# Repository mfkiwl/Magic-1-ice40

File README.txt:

These boards are designed to replicate Bill Buzbee's Magic-1 computer at 

http://www.homebrewcpu.com

They are licenced as Open Source Hardware

https://en.wikipedia.org/wiki/Open-source_hardware

Notes:

Cards are 160x233 euro card with 2 DIN 41612 C96 connectors

They are designed to be used in a Schroff EuropacPRO enclosure

The holes on the outside edge of the card (opposite to the connectors)
are designed to accept the Schroff card extractors ref 24560-378
You will also need to add ref 24560-377 for each card slot for this to work

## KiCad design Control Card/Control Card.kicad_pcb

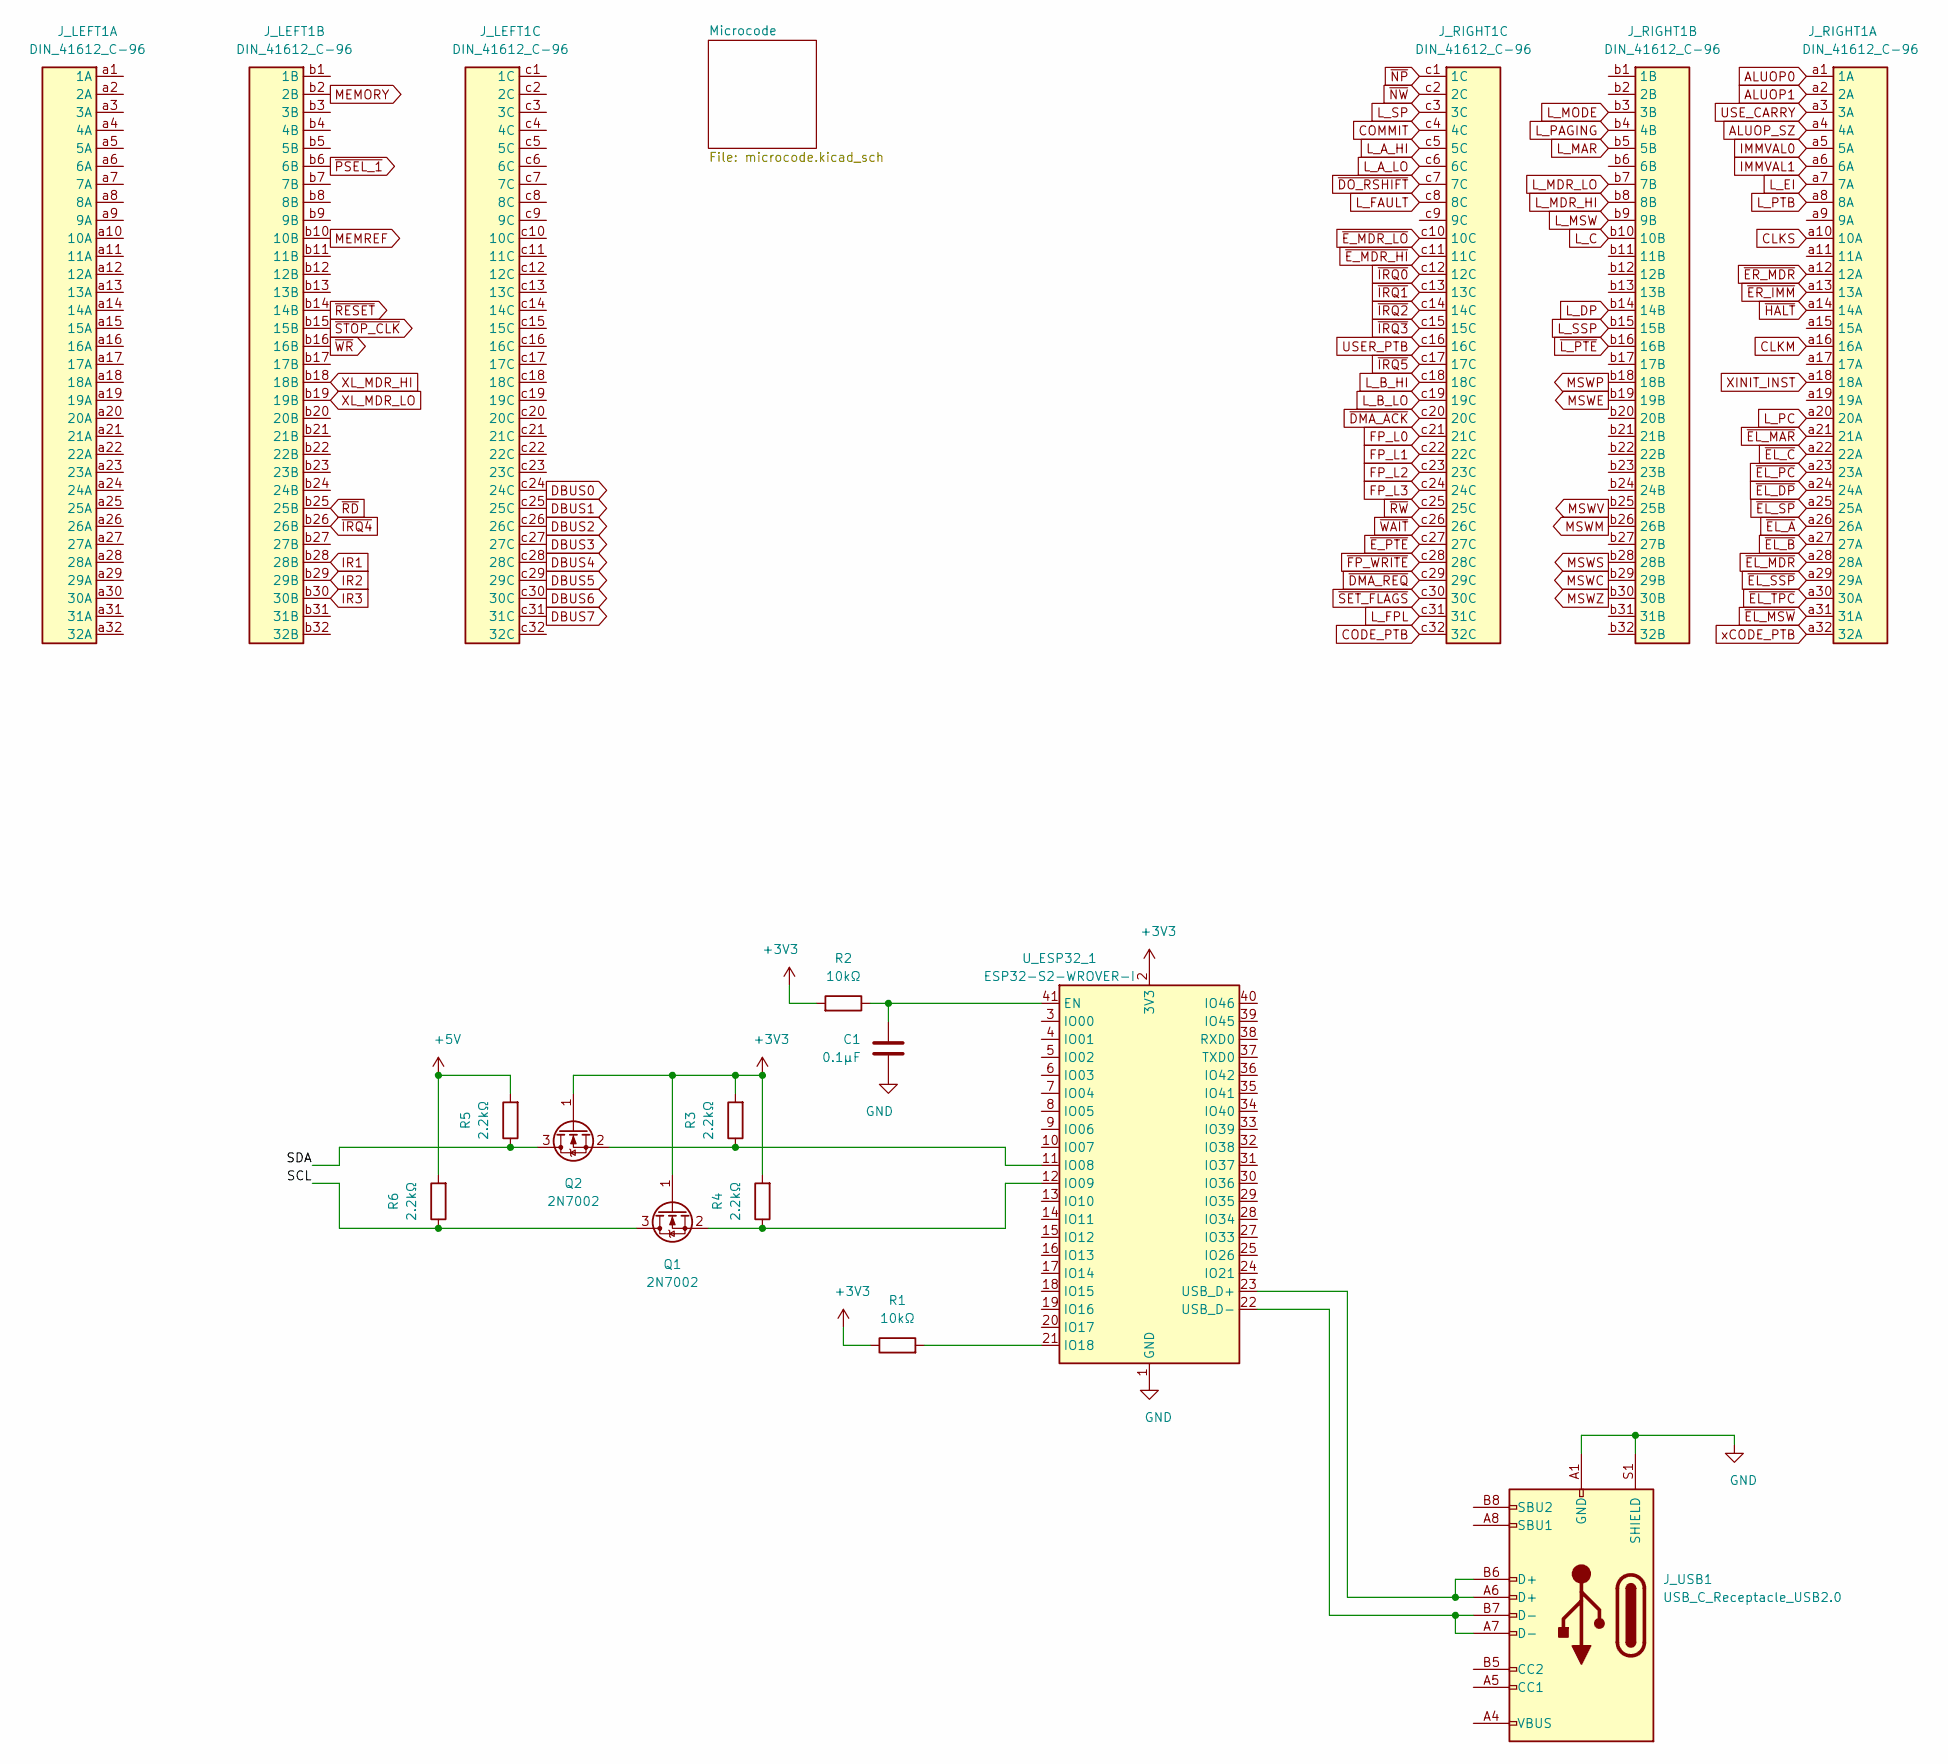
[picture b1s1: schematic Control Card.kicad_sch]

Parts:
C1: 0.1µF; C_0805_2012Metric
J_LEFT1: DIN_41612_C-96; DIN41612_C_3x32_Male_Horizontal_THT
J_RIGHT1: DIN_41612_C-96; DIN41612_C_3x32_Male_Horizontal_THT
J_USB1: USB_C_Receptacle_USB2.0; USB_C_Receptacle_GCT_USB4085
Q1, Q2: 2N7002; SOT-23
R1, R2: 10kΩ; R_0805_2012Metric
R3, R4, R5, R6: 2.2kΩ; R_0805_2012Metric
U_ESP32_1: ESP32-S2-WROVER-I; ESP32-S2-WROVER

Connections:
+3V3: Q1.1 (G), Q2.1 (G), R1.1, R2.2, R3.2, R4.2, U_ESP32_1.2 (3V3)
+5V: R5.2, R6.2; also elsewhere on the board
/SCL: Q1.3 (D), R6.1
/SDA: Q2.3 (D), R5.1
ALUOP0: J_RIGHT1.a1 (1A)
ALUOP1: J_RIGHT1.a2 (2A)
ALUOP_SZ: J_RIGHT1.a4 (4A)
CLKM: J_RIGHT1.a16 (16A)
CLKS: J_RIGHT1.a10 (10A)
CODE_PTB: J_RIGHT1.c32 (32C)
COMMIT: J_RIGHT1.c4 (4C)
DBUS0: J_LEFT1.c24 (24C); also elsewhere on the board
DBUS1: J_LEFT1.c25 (25C); also elsewhere on the board
DBUS2: J_LEFT1.c26 (26C); also elsewhere on the board
DBUS3: J_LEFT1.c27 (27C); also elsewhere on the board
DBUS4: J_LEFT1.c28 (28C); also elsewhere on the board
DBUS5: J_LEFT1.c29 (29C); also elsewhere on the board
DBUS6: J_LEFT1.c30 (30C); also elsewhere on the board
DBUS7: J_LEFT1.c31 (31C); also elsewhere on the board
FP_L0: J_RIGHT1.c21 (21C)
FP_L1: J_RIGHT1.c22 (22C)
FP_L2: J_RIGHT1.c23 (23C)
FP_L3: J_RIGHT1.c24 (24C)
GND: C1.2, J_USB1.A1 (GND), J_USB1.A12 (GND), J_USB1.B1 (GND), J_USB1.B12 (GND), J_USB1.S1 (SHIELD), U_ESP32_1.1 (GND), U_ESP32_1.26 (GND), U_ESP32_1.42 (GND), U_ESP32_1.43 (GND); also elsewhere on the board
IMMVAL0: J_RIGHT1.a5 (5A)
IMMVAL1: J_RIGHT1.a6 (6A)
IR1: J_LEFT1.b28 (28B); also elsewhere on the board
IR2: J_LEFT1.b29 (29B); also elsewhere on the board
IR3: J_LEFT1.b30 (30B); also elsewhere on the board
L_A_HI: J_RIGHT1.c5 (5C)
L_A_LO: J_RIGHT1.c6 (6C)
L_B_HI: J_RIGHT1.c18 (18C)
L_B_LO: J_RIGHT1.c19 (19C)
L_C: J_RIGHT1.b10 (10B)
L_DP: J_RIGHT1.b14 (14B)
L_EI: J_RIGHT1.a7 (7A)
L_FAULT: J_RIGHT1.c8 (8C)
L_FPL: J_RIGHT1.c31 (31C)
L_MAR: J_RIGHT1.b5 (5B)
L_MDR_HI: J_RIGHT1.b8 (8B)
L_MDR_LO: J_RIGHT1.b7 (7B)
L_MODE: J_RIGHT1.b3 (3B)
L_MSW: J_RIGHT1.b9 (9B)
L_PAGING: J_RIGHT1.b4 (4B)
L_PC: J_RIGHT1.a20 (20A)
L_PTB: J_RIGHT1.a8 (8A)
L_SP: J_RIGHT1.c3 (3C)
L_SSP: J_RIGHT1.b15 (15B)
MEMORY: J_LEFT1.b2 (2B)
MEMREF: J_LEFT1.b10 (10B)
MSWC: J_RIGHT1.b29 (29B); also elsewhere on the board
MSWE: J_RIGHT1.b19 (19B)
MSWM: J_RIGHT1.b26 (26B)
MSWP: J_RIGHT1.b18 (18B)
MSWS: J_RIGHT1.b28 (28B); also elsewhere on the board
MSWV: J_RIGHT1.b25 (25B); also elsewhere on the board
MSWZ: J_RIGHT1.b30 (30B); also elsewhere on the board
unnamed: C1.1, R2.1, U_ESP32_1.41 (EN)
unnamed: J_USB1.A4 (VBUS), J_USB1.A9 (VBUS), J_USB1.B4 (VBUS), J_USB1.B9 (VBUS)
unnamed: J_USB1.A6 (D+), J_USB1.B6 (D+), U_ESP32_1.23 (USB_D+)
unnamed: J_USB1.A7 (D-), J_USB1.B7 (D-), U_ESP32_1.22 (USB_D-)
unnamed: Q1.2 (S), R4.1, U_ESP32_1.12 (IO09)
unnamed: Q2.2 (S), R3.1, U_ESP32_1.11 (IO08)
unnamed: R1.2, U_ESP32_1.21 (IO18)
USER_PTB: J_RIGHT1.c16 (16C)
USE_CARRY: J_RIGHT1.a3 (3A)
XINIT_INST: J_RIGHT1.a18 (18A)
XL_MDR_HI: J_LEFT1.b18 (18B)
XL_MDR_LO: J_LEFT1.b19 (19B)
xCODE_PTB: J_RIGHT1.a32 (32A)
~DMA_ACK~: J_RIGHT1.c20 (20C)
~DMA_REQ~: J_RIGHT1.c29 (29C)
~DO_RSHIFT~: J_RIGHT1.c7 (7C)
~EL_A~: J_RIGHT1.a26 (26A)
~EL_B~: J_RIGHT1.a27 (27A)
~EL_C~: J_RIGHT1.a22 (22A)
~EL_DP~: J_RIGHT1.a24 (24A)
~EL_MAR~: J_RIGHT1.a21 (21A)
~EL_MDR~: J_RIGHT1.a28 (28A)
~EL_MSW~: J_RIGHT1.a31 (31A)
~EL_PC~: J_RIGHT1.a23 (23A)
~EL_SP~: J_RIGHT1.a25 (25A)
~EL_SSP~: J_RIGHT1.a29 (29A)
~EL_TPC~: J_RIGHT1.a30 (30A)
~ER_IMM~: J_RIGHT1.a13 (13A)
~ER_MDR~: J_RIGHT1.a12 (12A)
~E_MDR_HI~: J_RIGHT1.c11 (11C)
~E_MDR_LO~: J_RIGHT1.c10 (10C)
~E_PTE~: J_RIGHT1.c27 (27C)
~FP_WRITE~: J_RIGHT1.c28 (28C)
~HALT~: J_RIGHT1.a14 (14A)
~IRQ0~: J_RIGHT1.c12 (12C)
~IRQ1~: J_RIGHT1.c13 (13C)
~IRQ2~: J_RIGHT1.c14 (14C)
~IRQ3~: J_RIGHT1.c15 (15C)
~IRQ4~: J_LEFT1.b26 (26B)
~IRQ5~: J_RIGHT1.c17 (17C)
~L_PTE~: J_RIGHT1.b16 (16B)
~NP~: J_RIGHT1.c1 (1C)
~NW~: J_RIGHT1.c2 (2C)
~PSEL_1~: J_LEFT1.b6 (6B)
~RD~: J_LEFT1.b25 (25B)
~RESET~: J_LEFT1.b14 (14B)
~RW~: J_RIGHT1.c25 (25C)
~SET_FLAGS~: J_RIGHT1.c30 (30C)
~STOP_CLK~: J_LEFT1.b15 (15B)
~WAIT~: J_RIGHT1.c26 (26C)
~WR~: J_LEFT1.b16 (16B)

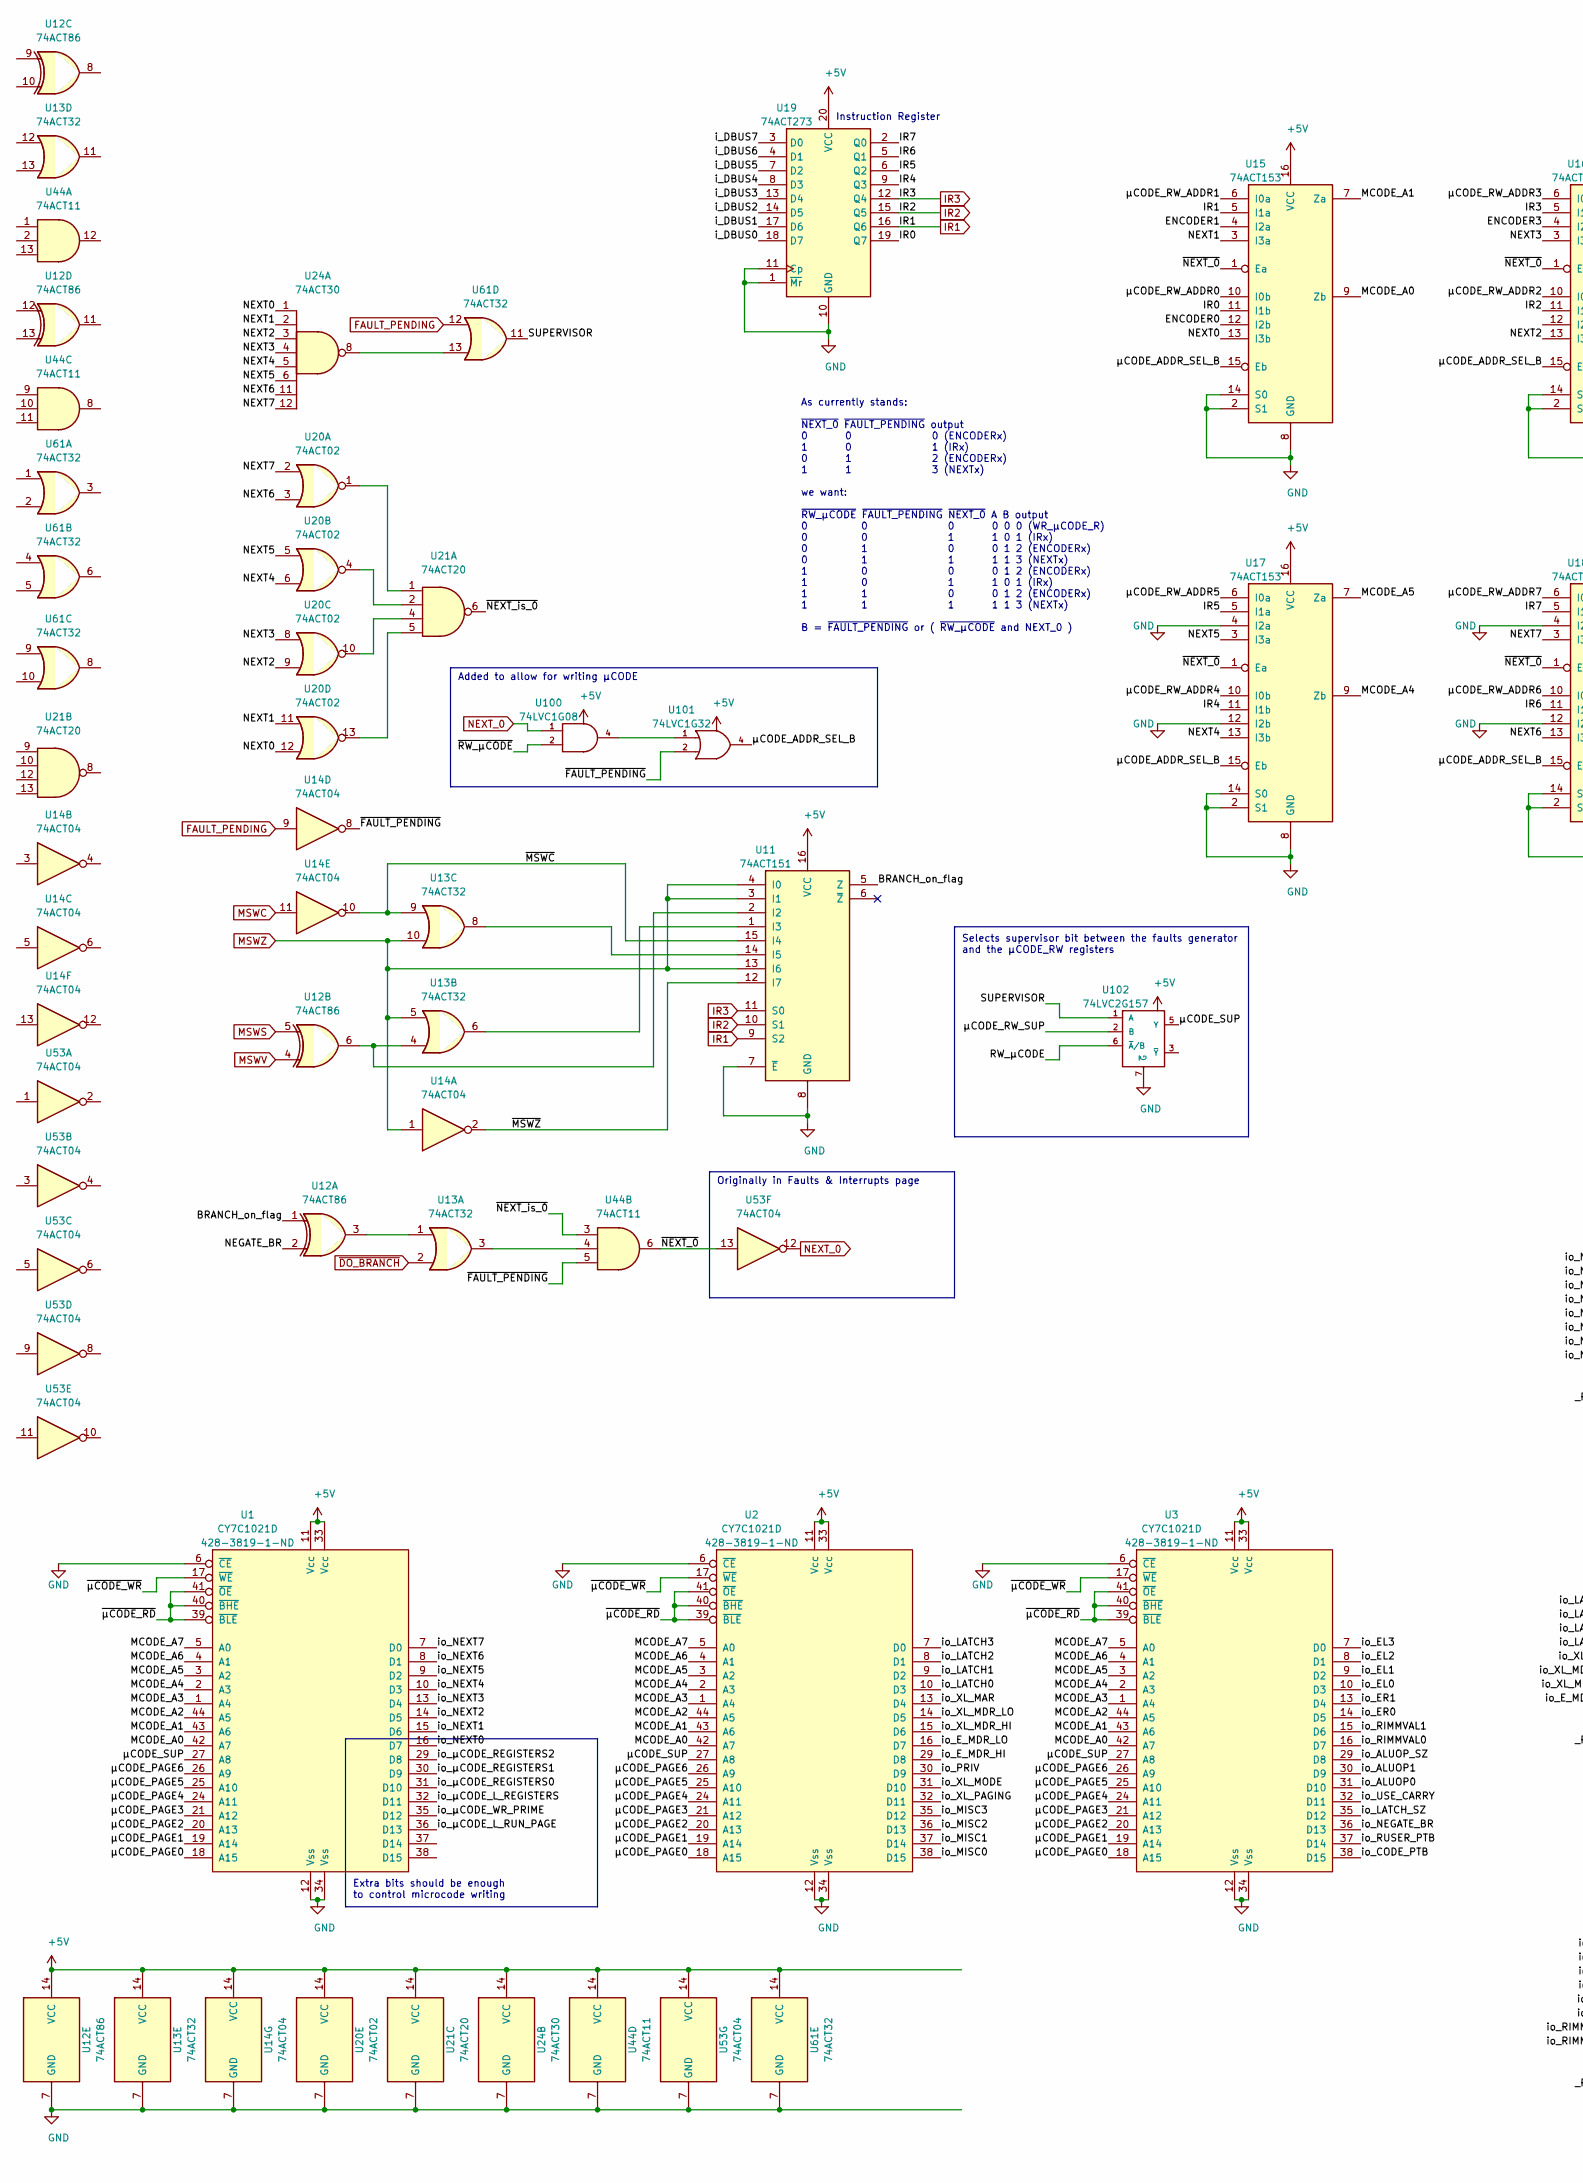
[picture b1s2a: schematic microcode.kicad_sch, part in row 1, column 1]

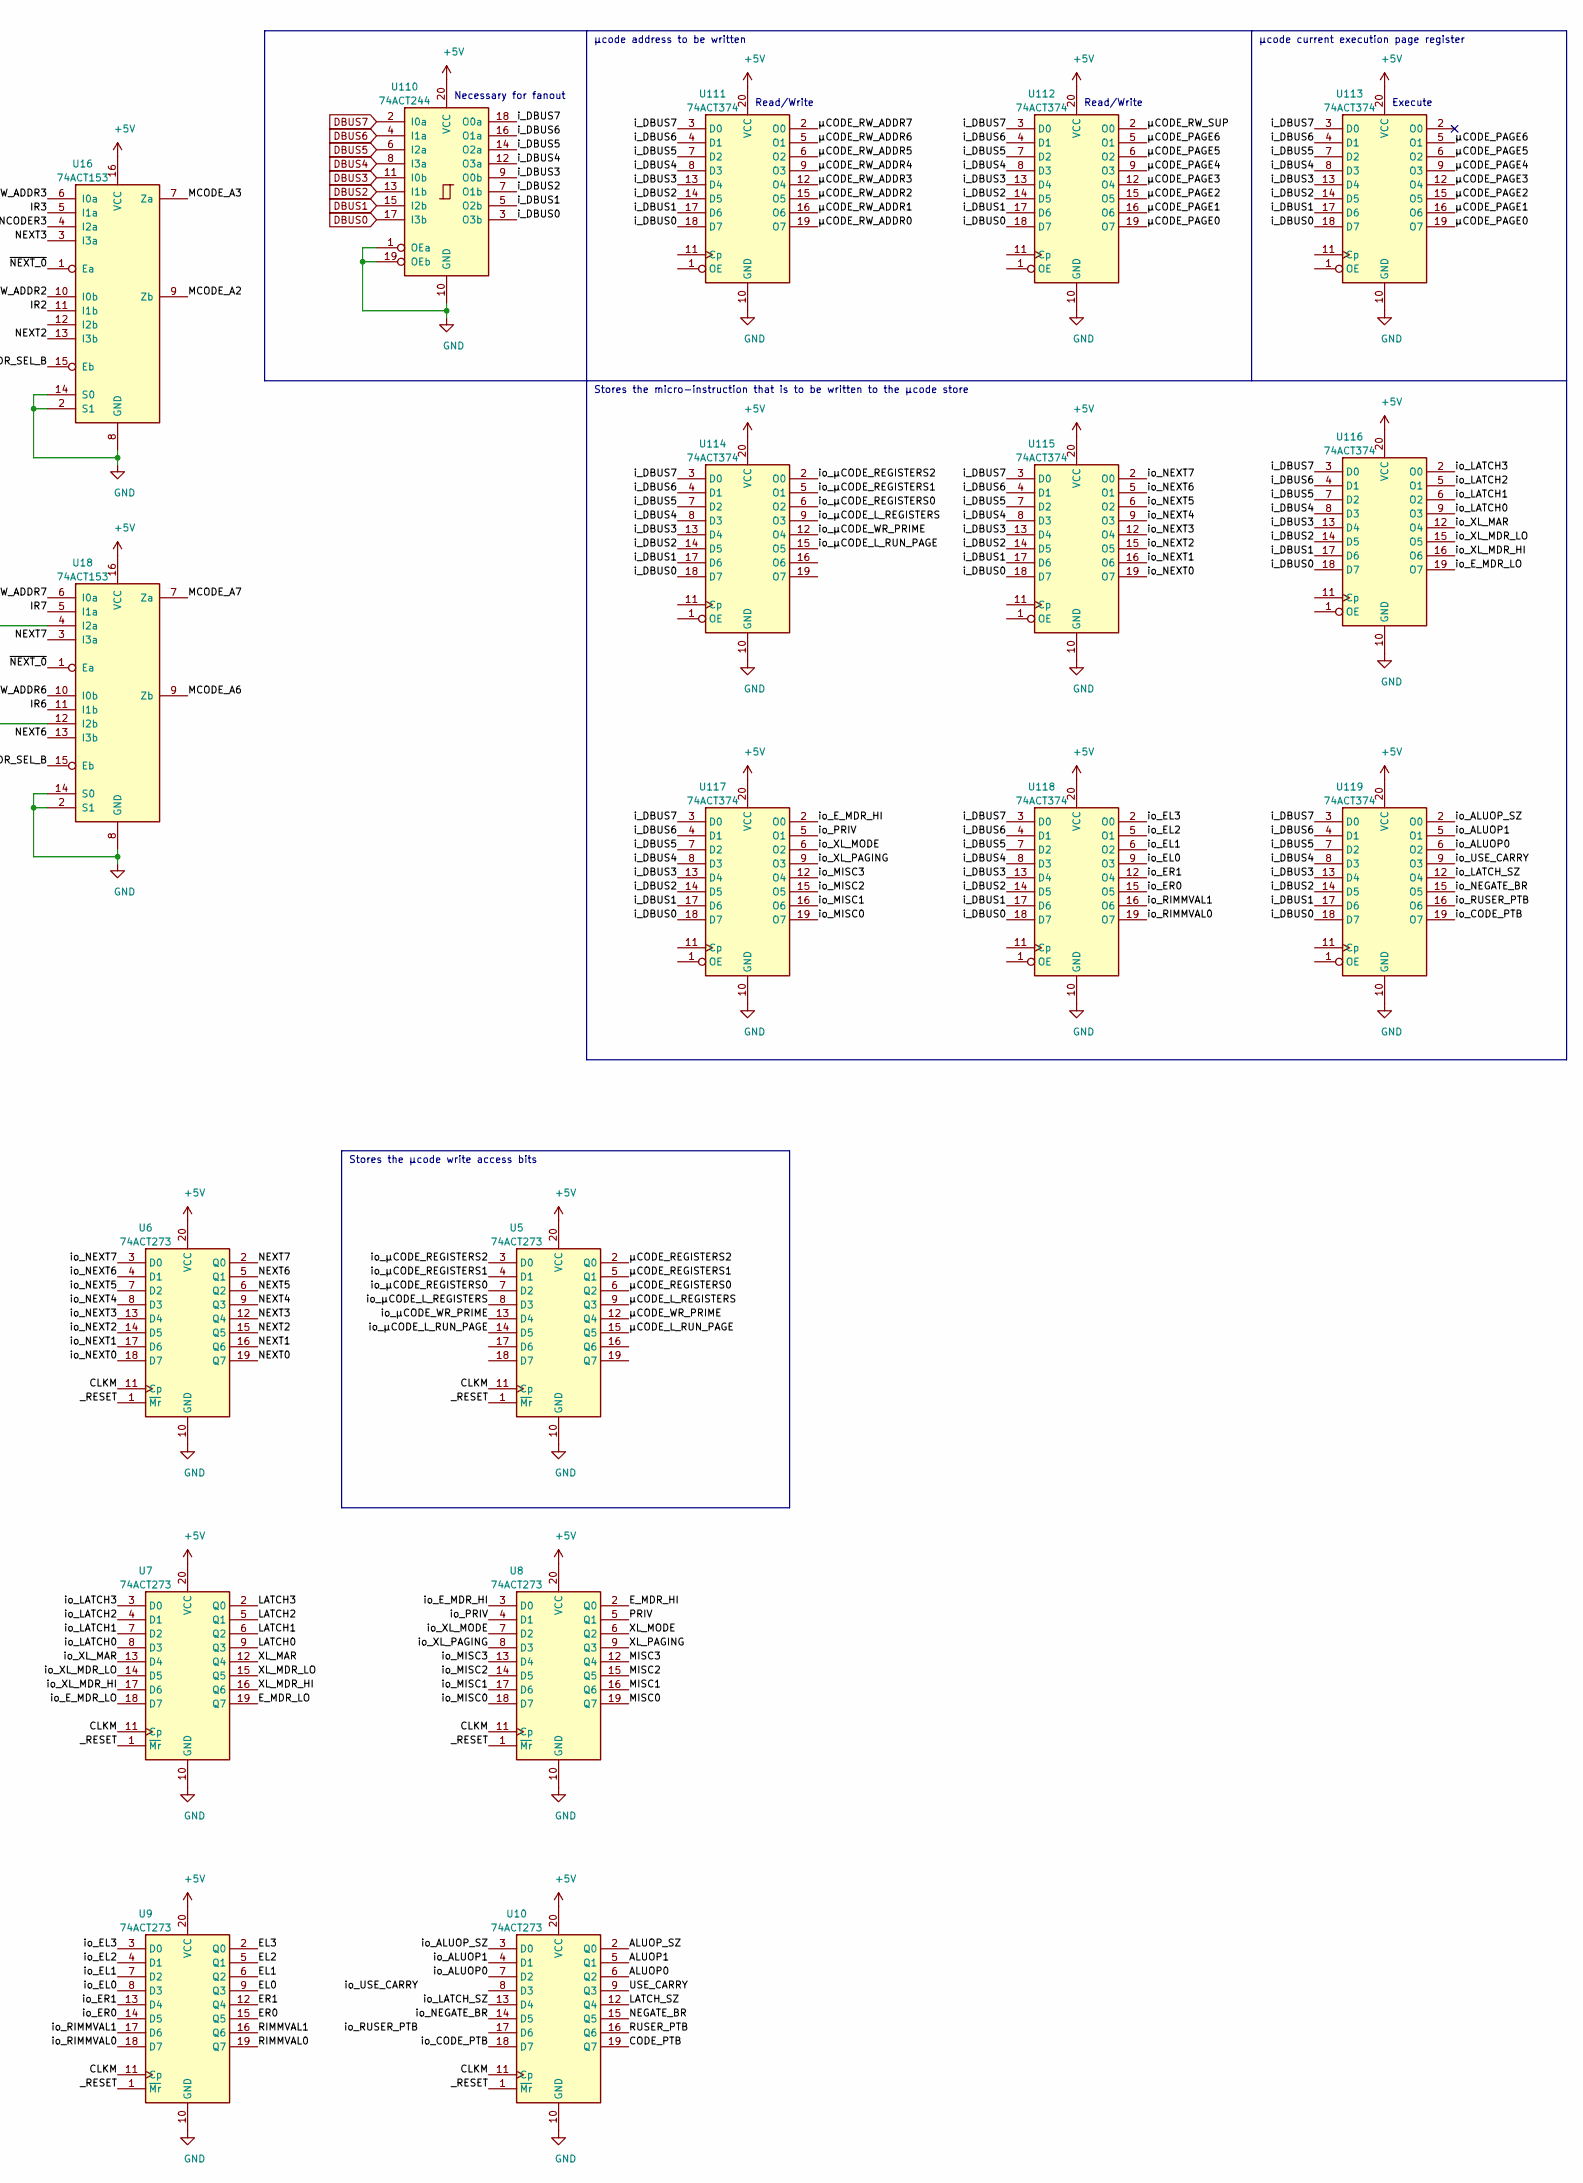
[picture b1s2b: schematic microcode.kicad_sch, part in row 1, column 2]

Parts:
U1, U2, U3: CY7C1021D; TSOP-II-44_10.16x18.41mm_P0.8mm; Digikey 428-3819-1-ND
U5, U6, U7, U8, U9, U10, U19: 74ACT273; SOIC-20W_7.5x12.8mm_P1.27mm
U11: 74ACT151; SOIC-16_3.9x9.9mm_P1.27mm
U12: 74ACT86; SOIC-14_3.9x8.7mm_P1.27mm
U13, U61: 74ACT32; SOIC-14_3.9x8.7mm_P1.27mm
U14, U53: 74ACT04; SOIC-14_3.9x8.7mm_P1.27mm
U15, U16, U17, U18: 74ACT153; SOIC-16_3.9x9.9mm_P1.27mm
U20: 74ACT02; SOIC-14_3.9x8.7mm_P1.27mm
U21: 74ACT20; SOIC-14_3.9x8.7mm_P1.27mm
U24: 74ACT30; SOIC-14_3.9x8.7mm_P1.27mm
U44: 74ACT11; SOIC-14_3.9x8.7mm_P1.27mm
U100: 74LVC1G08; SOT-23-5
U101: 74LVC1G32; SOT-23-5
U102: 74LVC2G157; SSOP-8_2.95x2.8mm_P0.65mm
U110: 74ACT244; SOIC-20W_7.5x12.8mm_P1.27mm
U111, U112, U113, U114, U115, U116, U117, U118, U119: 74ACT374; SOIC-20W_7.5x12.8mm_P1.27mm

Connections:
+5V: U1.11 (Vcc), U1.33 (Vcc), U2.11 (Vcc), U2.33 (Vcc), U3.11 (Vcc), U3.33 (Vcc), U5.20 (VCC), U6.20 (VCC), U7.20 (VCC), U8.20 (VCC), U9.20 (VCC), U10.20 (VCC), U11.16 (VCC), U12.14 (VCC), U13.14 (VCC), U14.14 (VCC), U15.16 (VCC), U16.16 (VCC), U17.16 (VCC), U18.16 (VCC), U19.20 (VCC), U20.14 (VCC), U21.14 (VCC), U24.14 (VCC), U44.14 (VCC), U53.14 (VCC), U61.14 (VCC), U100.5 (VCC), U101.5 (VCC), U102.8 (VCC), U110.20 (VCC), U111.20 (VCC), U112.20 (VCC), U113.20 (VCC), U114.20 (VCC), U115.20 (VCC), U116.20 (VCC), U117.20 (VCC), U118.20 (VCC), U119.20 (VCC); also elsewhere on the board
/Microcode/ALUOP0: U10.6 (Q2)
/Microcode/ALUOP1: U10.5 (Q1)
/Microcode/ALUOP_SZ: U10.2 (Q0)
/Microcode/BRANCH_on_flag: U11.5 (Z), U12.1
/Microcode/CLKM: U5.11 (Cp), U6.11 (Cp), U7.11 (Cp), U8.11 (Cp), U9.11 (Cp), U10.11 (Cp)
/Microcode/CODE_PTB: U10.19 (Q7)
/Microcode/EL0: U9.9 (Q3)
/Microcode/EL1: U9.6 (Q2)
/Microcode/EL2: U9.5 (Q1)
/Microcode/EL3: U9.2 (Q0)
/Microcode/ENCODER0: U15.12 (I2b)
/Microcode/ENCODER1: U15.4 (I2a)
/Microcode/ENCODER3: U16.4 (I2a)
/Microcode/ER0: U9.15 (Q5)
/Microcode/ER1: U9.12 (Q4)
/Microcode/E_MDR_HI: U8.2 (Q0)
/Microcode/E_MDR_LO: U7.19 (Q7)
/Microcode/IR0: U15.11 (I1b), U19.19 (Q7)
/Microcode/IR4: U17.11 (I1b), U19.9 (Q3)
/Microcode/IR5: U17.5 (I1a), U19.6 (Q2)
/Microcode/IR6: U18.11 (I1b), U19.5 (Q1)
/Microcode/IR7: U18.5 (I1a), U19.2 (Q0)
/Microcode/LATCH0: U7.9 (Q3)
/Microcode/LATCH1: U7.6 (Q2)
/Microcode/LATCH2: U7.5 (Q1)
/Microcode/LATCH3: U7.2 (Q0)
/Microcode/LATCH_SZ: U10.12 (Q4)
/Microcode/MCODE_A0: U1.42 (A7), U2.42 (A7), U3.42 (A7), U15.9 (Zb)
/Microcode/MCODE_A1: U1.43 (A6), U2.43 (A6), U3.43 (A6), U15.7 (Za)
/Microcode/MCODE_A2: U1.44 (A5), U2.44 (A5), U3.44 (A5), U16.9 (Zb)
/Microcode/MCODE_A3: U1.1 (A4), U2.1 (A4), U3.1 (A4), U16.7 (Za)
/Microcode/MCODE_A4: U1.2 (A3), U2.2 (A3), U3.2 (A3), U17.9 (Zb)
/Microcode/MCODE_A5: U1.3 (A2), U2.3 (A2), U3.3 (A2), U17.7 (Za)
/Microcode/MCODE_A6: U1.4 (A1), U2.4 (A1), U3.4 (A1), U18.9 (Zb)
/Microcode/MCODE_A7: U1.5 (A0), U2.5 (A0), U3.5 (A0), U18.7 (Za)
/Microcode/MISC0: U8.19 (Q7)
/Microcode/MISC1: U8.16 (Q6)
/Microcode/MISC2: U8.15 (Q5)
/Microcode/MISC3: U8.12 (Q4)
/Microcode/NEGATE_BR: U10.15 (Q5), U12.2
/Microcode/NEXT0: U6.19 (Q7), U15.13 (I3b), U20.12, U24.1
/Microcode/NEXT1: U6.16 (Q6), U15.3 (I3a), U20.11, U24.2
/Microcode/NEXT2: U6.15 (Q5), U16.13 (I3b), U20.9, U24.3
/Microcode/NEXT3: U6.12 (Q4), U16.3 (I3a), U20.8, U24.4
/Microcode/NEXT4: U6.9 (Q3), U17.13 (I3b), U20.6, U24.5
/Microcode/NEXT5: U6.6 (Q2), U17.3 (I3a), U20.5, U24.6
/Microcode/NEXT6: U6.5 (Q1), U18.13 (I3b), U20.3, U24.11
/Microcode/NEXT7: U6.2 (Q0), U18.3 (I3a), U20.2, U24.12
/Microcode/PRIV: U8.5 (Q1)
/Microcode/RIMMVAL0: U9.19 (Q7)
/Microcode/RIMMVAL1: U9.16 (Q6)
/Microcode/RUSER_PTB: U10.16 (Q6)
/Microcode/RW_µCODE: U102.6 (~A~/B)
/Microcode/SUPERVISOR: U61.11, U102.1 (A)
/Microcode/USE_CARRY: U10.9 (Q3)
/Microcode/XL_MAR: U7.12 (Q4)
/Microcode/XL_MDR_HI: U7.16 (Q6)
/Microcode/XL_MDR_LO: U7.15 (Q5)
/Microcode/XL_MODE: U8.6 (Q2)
/Microcode/XL_PAGING: U8.9 (Q3)
/Microcode/_RESET: U5.1 (~Mr), U6.1 (~Mr), U7.1 (~Mr), U8.1 (~Mr), U9.1 (~Mr), U10.1 (~Mr)
/Microcode/i_DBUS0: U19.18 (D7), U110.3 (O3b), U111.18 (D7), U112.18 (D7), U113.18 (D7), U114.18 (D7), U115.18 (D7), U116.18 (D7), U117.18 (D7), U118.18 (D7), U119.18 (D7)
/Microcode/i_DBUS1: U19.17 (D6), U110.5 (O2b), U111.17 (D6), U112.17 (D6), U113.17 (D6), U114.17 (D6), U115.17 (D6), U116.17 (D6), U117.17 (D6), U118.17 (D6), U119.17 (D6)
/Microcode/i_DBUS2: U19.14 (D5), U110.7 (O1b), U111.14 (D5), U112.14 (D5), U113.14 (D5), U114.14 (D5), U115.14 (D5), U116.14 (D5), U117.14 (D5), U118.14 (D5), U119.14 (D5)
/Microcode/i_DBUS3: U19.13 (D4), U110.9 (O0b), U111.13 (D4), U112.13 (D4), U113.13 (D4), U114.13 (D4), U115.13 (D4), U116.13 (D4), U117.13 (D4), U118.13 (D4), U119.13 (D4)
/Microcode/i_DBUS4: U19.8 (D3), U110.12 (O3a), U111.8 (D3), U112.8 (D3), U113.8 (D3), U114.8 (D3), U115.8 (D3), U116.8 (D3), U117.8 (D3), U118.8 (D3), U119.8 (D3)
/Microcode/i_DBUS5: U19.7 (D2), U110.14 (O2a), U111.7 (D2), U112.7 (D2), U113.7 (D2), U114.7 (D2), U115.7 (D2), U116.7 (D2), U117.7 (D2), U118.7 (D2), U119.7 (D2)
/Microcode/i_DBUS6: U19.4 (D1), U110.16 (O1a), U111.4 (D1), U112.4 (D1), U113.4 (D1), U114.4 (D1), U115.4 (D1), U116.4 (D1), U117.4 (D1), U118.4 (D1), U119.4 (D1)
/Microcode/i_DBUS7: U19.3 (D0), U110.18 (O0a), U111.3 (D0), U112.3 (D0), U113.3 (D0), U114.3 (D0), U115.3 (D0), U116.3 (D0), U117.3 (D0), U118.3 (D0), U119.3 (D0)
/Microcode/io_ALUOP0: U3.31 (D10), U10.7 (D2), U119.6 (O2)
/Microcode/io_ALUOP1: U3.30 (D9), U10.4 (D1), U119.5 (O1)
/Microcode/io_ALUOP_SZ: U3.29 (D8), U10.3 (D0), U119.2 (O0)
/Microcode/io_CODE_PTB: U3.38 (D15), U10.18 (D7), U119.19 (O7)
/Microcode/io_EL0: U3.10 (D3), U9.8 (D3), U118.9 (O3)
/Microcode/io_EL1: U3.9 (D2), U9.7 (D2), U118.6 (O2)
/Microcode/io_EL2: U3.8 (D1), U9.4 (D1), U118.5 (O1)
/Microcode/io_EL3: U3.7 (D0), U9.3 (D0), U118.2 (O0)
/Microcode/io_ER0: U3.14 (D5), U9.14 (D5), U118.15 (O5)
/Microcode/io_ER1: U3.13 (D4), U9.13 (D4), U118.12 (O4)
/Microcode/io_E_MDR_HI: U2.29 (D8), U8.3 (D0), U117.2 (O0)
/Microcode/io_E_MDR_LO: U2.16 (D7), U7.18 (D7), U116.19 (O7)
/Microcode/io_LATCH0: U2.10 (D3), U7.8 (D3), U116.9 (O3)
/Microcode/io_LATCH1: U2.9 (D2), U7.7 (D2), U116.6 (O2)
/Microcode/io_LATCH2: U2.8 (D1), U7.4 (D1), U116.5 (O1)
/Microcode/io_LATCH3: U2.7 (D0), U7.3 (D0), U116.2 (O0)
/Microcode/io_LATCH_SZ: U3.35 (D12), U10.13 (D4), U119.12 (O4)
/Microcode/io_MISC0: U2.38 (D15), U8.18 (D7), U117.19 (O7)
/Microcode/io_MISC1: U2.37 (D14), U8.17 (D6), U117.16 (O6)
/Microcode/io_MISC2: U2.36 (D13), U8.14 (D5), U117.15 (O5)
/Microcode/io_MISC3: U2.35 (D12), U8.13 (D4), U117.12 (O4)
/Microcode/io_NEGATE_BR: U3.36 (D13), U10.14 (D5), U119.15 (O5)
/Microcode/io_NEXT0: U1.16 (D7), U6.18 (D7), U115.19 (O7)
/Microcode/io_NEXT1: U1.15 (D6), U6.17 (D6), U115.16 (O6)
/Microcode/io_NEXT2: U1.14 (D5), U6.14 (D5), U115.15 (O5)
/Microcode/io_NEXT3: U1.13 (D4), U6.13 (D4), U115.12 (O4)
/Microcode/io_NEXT4: U1.10 (D3), U6.8 (D3), U115.9 (O3)
/Microcode/io_NEXT5: U1.9 (D2), U6.7 (D2), U115.6 (O2)
/Microcode/io_NEXT6: U1.8 (D1), U6.4 (D1), U115.5 (O1)
/Microcode/io_NEXT7: U1.7 (D0), U6.3 (D0), U115.2 (O0)
/Microcode/io_PRIV: U2.30 (D9), U8.4 (D1), U117.5 (O1)
/Microcode/io_RIMMVAL0: U3.16 (D7), U9.18 (D7), U118.19 (O7)
/Microcode/io_RIMMVAL1: U3.15 (D6), U9.17 (D6), U118.16 (O6)
/Microcode/io_RUSER_PTB: U3.37 (D14), U119.16 (O6)
/Microcode/io_USE_CARRY: U3.32 (D11), U119.9 (O3)
/Microcode/io_XL_MAR: U2.13 (D4), U7.13 (D4), U116.12 (O4)
/Microcode/io_XL_MDR_HI: U2.15 (D6), U7.17 (D6), U116.16 (O6)
/Microcode/io_XL_MDR_LO: U2.14 (D5), U7.14 (D5), U116.15 (O5)
/Microcode/io_XL_MODE: U2.31 (D10), U8.7 (D2), U117.6 (O2)
/Microcode/io_XL_PAGING: U2.32 (D11), U8.8 (D3), U117.9 (O3)
/Microcode/io_µCODE_L_REGISTERS: U1.32 (D11), U5.8 (D3), U114.9 (O3)
/Microcode/io_µCODE_L_RUN_PAGE: U1.36 (D13), U5.14 (D5), U114.15 (O5)
/Microcode/io_µCODE_REGISTERS0: U1.31 (D10), U5.7 (D2), U114.6 (O2)
/Microcode/io_µCODE_REGISTERS1: U1.30 (D9), U5.4 (D1), U114.5 (O1)
/Microcode/io_µCODE_REGISTERS2: U1.29 (D8), U5.3 (D0), U114.2 (O0)
/Microcode/io_µCODE_WR_PRIME: U1.35 (D12), U5.13 (D4), U114.12 (O4)
/Microcode/~FAULT_PENDING~: U14.8, U44.5, U101.2
/Microcode/~MSWC~: U11.15 (I4), U13.9, U14.10
/Microcode/~MSWZ~: U11.12 (I7), U14.2
/Microcode/~NEXT_0~: U15.1 (Ea), U16.1 (Ea), U17.1 (Ea), U18.1 (Ea), U44.6, U53.13
/Microcode/~NEXT_is_0~: U21.6, U44.3
/Microcode/~RW_µCODE~: U100.2
/Microcode/~µCODE_RD~: U1.39 (~BLE~), U1.40 (~BHE~), U1.41 (~OE~), U2.39 (~BLE~), U2.40 (~BHE~), U2.41 (~OE~), U3.39 (~BLE~), U3.40 (~BHE~), U3.41 (~OE~)
/Microcode/~µCODE_WR~: U1.17 (~WE~), U2.17 (~WE~), U3.17 (~WE~)
/Microcode/µCODE_ADDR_SEL_B: U15.15 (Eb), U16.15 (Eb), U17.15 (Eb), U18.15 (Eb), U101.4
/Microcode/µCODE_L_REGISTERS: U5.9 (Q3)
/Microcode/µCODE_L_RUN_PAGE: U5.15 (Q5)
/Microcode/µCODE_PAGE0: U1.18 (A15), U2.18 (A15), U3.18 (A15), U112.19 (O7), U113.19 (O7)
/Microcode/µCODE_PAGE1: U1.19 (A14), U2.19 (A14), U3.19 (A14), U112.16 (O6), U113.16 (O6)
/Microcode/µCODE_PAGE2: U1.20 (A13), U2.20 (A13), U3.20 (A13), U112.15 (O5), U113.15 (O5)
/Microcode/µCODE_PAGE3: U1.21 (A12), U2.21 (A12), U3.21 (A12), U112.12 (O4), U113.12 (O4)
/Microcode/µCODE_PAGE4: U1.24 (A11), U2.24 (A11), U3.24 (A11), U112.9 (O3), U113.9 (O3)
/Microcode/µCODE_PAGE5: U1.25 (A10), U2.25 (A10), U3.25 (A10), U112.6 (O2), U113.6 (O2)
/Microcode/µCODE_PAGE6: U1.26 (A9), U2.26 (A9), U3.26 (A9), U112.5 (O1), U113.5 (O1)
/Microcode/µCODE_REGISTERS0: U5.6 (Q2)
/Microcode/µCODE_REGISTERS1: U5.5 (Q1)
/Microcode/µCODE_REGISTERS2: U5.2 (Q0)
/Microcode/µCODE_RW_ADDR0: U15.10 (I0b), U111.19 (O7)
/Microcode/µCODE_RW_ADDR1: U15.6 (I0a), U111.16 (O6)
/Microcode/µCODE_RW_ADDR2: U16.10 (I0b), U111.15 (O5)
/Microcode/µCODE_RW_ADDR3: U16.6 (I0a), U111.12 (O4)
/Microcode/µCODE_RW_ADDR4: U17.10 (I0b), U111.9 (O3)
/Microcode/µCODE_RW_ADDR5: U17.6 (I0a), U111.6 (O2)
/Microcode/µCODE_RW_ADDR6: U18.10 (I0b), U111.5 (O1)
/Microcode/µCODE_RW_ADDR7: U18.6 (I0a), U111.2 (O0)
/Microcode/µCODE_RW_SUP: U102.2 (B), U112.2 (O0)
/Microcode/µCODE_SUP: U1.27 (A8), U2.27 (A8), U3.27 (A8), U102.5 (Y)
/Microcode/µCODE_WR_PRIME: U5.12 (Q4)
DBUS0: U110.17 (I3b); also elsewhere on the board
DBUS1: U110.15 (I2b); also elsewhere on the board
DBUS2: U110.13 (I1b); also elsewhere on the board
DBUS3: U110.11 (I0b); also elsewhere on the board
DBUS4: U110.8 (I3a); also elsewhere on the board
DBUS5: U110.6 (I2a); also elsewhere on the board
DBUS6: U110.4 (I1a); also elsewhere on the board
DBUS7: U110.2 (I0a); also elsewhere on the board
FAULT_PENDING: U14.9, U61.12
GND: U1.6 (~CE~), U1.12 (Vss), U1.34 (Vss), U2.6 (~CE~), U2.12 (Vss), U2.34 (Vss), U3.6 (~CE~), U3.12 (Vss), U3.34 (Vss), U5.10 (GND), U6.10 (GND), U7.10 (GND), U8.10 (GND), U9.10 (GND), U10.10 (GND), U11.7 (~E), U11.8 (GND), U12.7 (GND), U13.7 (GND), U14.7 (GND), U15.2 (S1), U15.8 (GND), U15.14 (S0), U16.2 (S1), U16.8 (GND), U16.14 (S0), U17.2 (S1), U17.4 (I2a), U17.8 (GND), U17.12 (I2b), U17.14 (S0), U18.2 (S1), U18.4 (I2a), U18.8 (GND), U18.12 (I2b), U18.14 (S0), U19.1 (~Mr), U19.10 (GND), U19.11 (Cp), U20.7 (GND), U21.7 (GND), U24.7 (GND), U44.7 (GND), U53.7 (GND), U61.7 (GND), U100.3 (GND), U101.3 (GND), U102.4 (GND), U102.7 (~G), U110.1 (OEa), U110.10 (GND), U110.19 (OEb), U111.10 (GND), U112.10 (GND), U113.10 (GND), U114.10 (GND), U115.10 (GND), U116.10 (GND), U117.10 (GND), U118.10 (GND), U119.10 (GND); also elsewhere on the board
IR1: U11.9 (S2), U15.5 (I1a), U19.16 (Q6); also elsewhere on the board
IR2: U11.10 (S1), U16.11 (I1b), U19.15 (Q5); also elsewhere on the board
IR3: U11.11 (S0), U16.5 (I1a), U19.12 (Q4); also elsewhere on the board
MSWC: U14.11; also elsewhere on the board
MSWS: U12.5; also elsewhere on the board
MSWV: U12.4; also elsewhere on the board
MSWZ: U11.3 (I1), U11.4 (I0), U11.13 (I6), U13.5, U13.10, U14.1; also elsewhere on the board
NEXT_0: U53.12, U100.1
unnamed: U11.1 (I3), U13.6
unnamed: U11.2 (I2), U12.6, U13.4
unnamed: U11.14 (I5), U13.8
unnamed: U12.3, U13.1
unnamed: U13.3, U44.4
unnamed: U20.1, U21.1
unnamed: U20.4, U21.2
unnamed: U20.10, U21.4
unnamed: U20.13, U21.5
unnamed: U24.8, U61.13
unnamed: U100.4, U101.1
~DO_BRANCH~: U13.2

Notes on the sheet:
Extra bits should be enough to control microcode writing
Added to allow for writing µCODE
Originally in Faults & Interrupts page
As currently stands: ~NEXT_0~ ~FAULT_PENDING~ output 0 0 0 (ENCODERx) 1 0 1 (IRx) 0 1 2 (ENCODERx) 1 1 3 (NEXTx) we want: ~RW_µCODE~ ~FAULT_PENDING~ ~NEXT_0~ A B output 0 0 0 0 0 0 (WR_µCODE_R) 0 0 1 1 0 1 (IRx) 0 1 0 0 1 2 (ENCODERx) 0 1 1 1 1 3 (NEXTx) 1 0 0 0 1 2 (ENCODERx) 1 0 1 1 0 1 (IRx) 1 1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
Instruction Register
Selects supervisor bit between the faults generator and the µCODE_RW registers
Stores the µcode write access bits
Necessary for fanout
µcode address to be written
Stores the micro-instruction that is to be written to the µcode store
Read/Write
µcode current execution page register
Execute

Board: 4 copper layers, 50 parts (0 on the bottom side), 145 nets, no tracks yet.

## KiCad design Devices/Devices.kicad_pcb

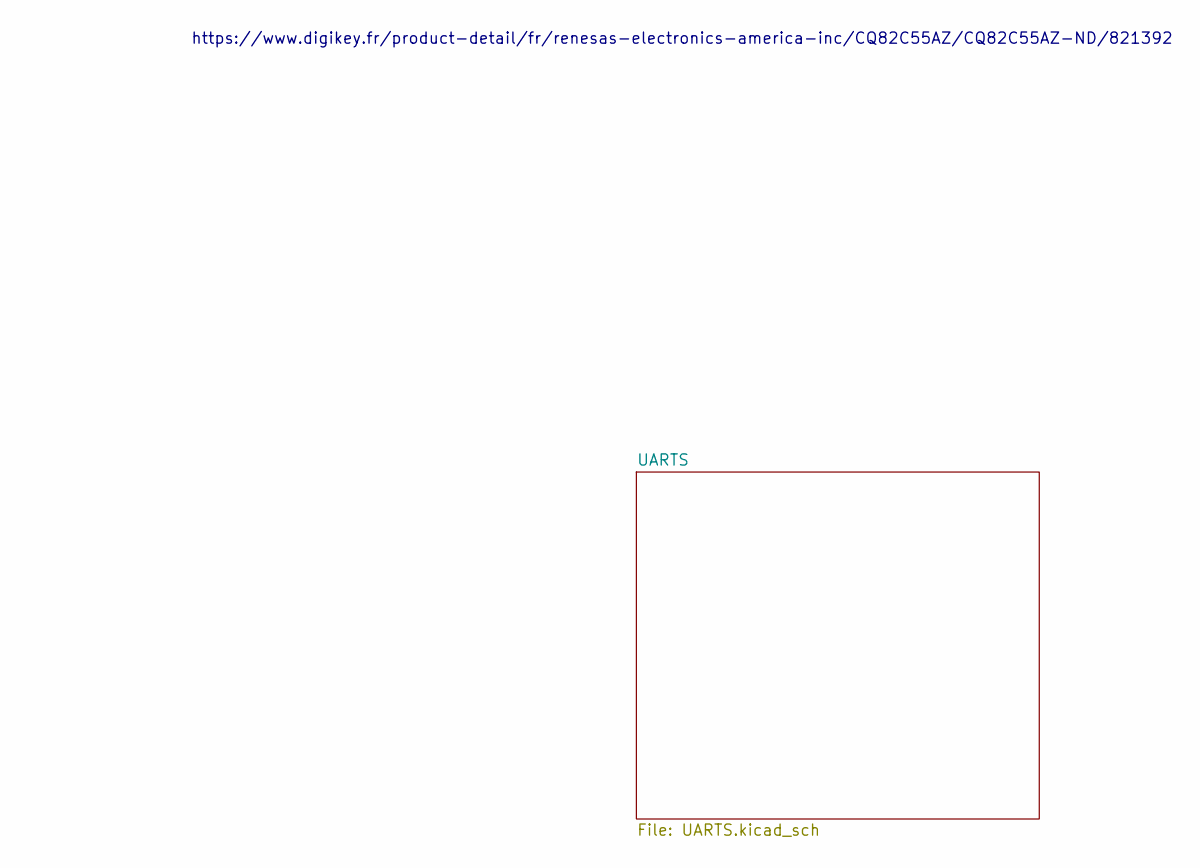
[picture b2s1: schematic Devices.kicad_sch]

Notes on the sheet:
https://www.digikey.fr/product-detail/fr/renesas-electronics-america-inc/CQ82C55AZ/CQ82C55AZ-ND/821392
